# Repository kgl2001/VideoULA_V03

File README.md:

# VideoULA V03 — BBC Micro Video ULA Replacement
## 44-pin Atmel ATF1504AS CPLD Version

This repository contains the hardware design and firmware for the VideoULA V03, a drop-in replacement for the VC2069 Video ULA (IC6) in the Acorn BBC Micro Model B and Master 128.

---

## Project Overview

The original BBC Micro Video ULA (IC6) is a custom ASIC that is no longer manufactured. Failed or missing ULAs result in a non-functional machine. This project provides a modern replacement using a CPLD and a small external SRAM for palette storage.

There are three hardware versions of this replacement, each in a separate repository:

| Version | CPLD | Macrocells | Tool | Repository |
|---|---|---|---|---|
| V01 | Xilinx XC9572XL-10-VQ44 | 72 | ISE 14.7 | [VideoULA_V01](https://github.com/kgl2001/VideoULA_V01) |
| V02 | Xilinx XC9572XL-10-VQ64 | 72 | ISE 14.7 | [VideoULA_V02](https://github.com/kgl2001/VideoULA_V02) |
| **V03** | Atmel ATF1504AS-10AU44 | 64 | Quartus 13.0 SP1 | This repo |

All three versions share the same 28-pin DIP footprint as the original ULA and are pin-compatible with the BBC Micro motherboard.

---

## V03 Hardware

- **CPLD**: Atmel ATF1504AS-10AU44 (64 macrocells, 5V) — still in production
- **SRAM**: ISSI IS62C256AL-45TLI (32K×8, 5V, TSOP-28, 45ns) — only locations 0-15 and bits 0-3 used
- **Oscillator**: 48MHz SMD oscillator (3225 package, 5V) — optional in 16MHz mode
- **Clock buffer**: 74LVC1G17 (SOT-23) — Schmitt trigger buffer on 16MHz CLK_IN
- **No LDO required** — everything runs at 5V

### Key differences from V01/V02

- **5V CPLD** — ATF1504AS operates at 5V throughout, no LDO required
- **Higher output voltage** — 5V logic outputs directly compatible with Master 128 custom ICs requiring higher logic 1 voltage; no output clock buffering needed
- **Still in production** — ATF1504AS is actively manufactured by Microchip, unlike the obsolete XC9572XL
- **64 macrocells** — slightly fewer than the XC9572XL's 72, but sufficient for the design (53/64 used in both the 48MHz and 16MHz builds)
- **Quartus 13.0 SP1** — uses Altera/Intel Quartus instead of Xilinx ISE
- **Separate CLK_16M and CLK_48M GCK pins** — no solder bridge needed to switch modes

### Hardware Revisions

| Revision | Status | Changes |
|---|---|---|
| Rev01 | Built and tested | Initial release |

---

## Firmware

The firmware is written in Verilog and built using Altera Quartus 13.0 SP1. The same Verilog source file (`CPLD Files/src/VideoULA.v`) is shared between V02 and V03.

The Quartus project targets the `EPM7064STC44-10` device — the Altera MAX7000S equivalent of the ATF1504AS, which Quartus supports natively. The `.pof` output is converted to a `.jed` file using the `pof2jed` utility for programming the ATF1504AS.

### Operating Modes

Two firmware builds are required — one per operating mode. Both CLK_16M and CLK_48M are wired to dedicated GCK pins, so no hardware changes are needed to switch modes — simply reprogram the CPLD with the appropriate `.jed` file.

#### 48MHz Mode (recommended)
- Uses the onboard 48MHz oscillator as the master clock
- Generates all BBC clock outputs (8/4/2/1MHz, CRTC, 6MHz) internally
- Provides clean, phase-locked 6MHz output for the SAA5050 teletext chip (tD ≈ 20ns ✓)
- Works reliably on all machines from cold power-up
- Build: uncomment `` `define CLK_48MHZ `` in `VideoULA.v`

#### 16MHz Mode
- Uses the BBC motherboard's 16MHz clock as the master clock (via Schmitt trigger buffer)
- The 48MHz oscillator is optional in 16MHz mode:
  - **Not fitted**: BBC's existing 6MHz circuit drives the SAA5050 as normal
  - **Fitted**: CPLD generates clean phase-locked 6MHz output (connect via IC37 replacement board)
- Build: uncomment `` `define CLK_16MHZ `` in `VideoULA.v`

### Quartus Build Instructions

1. Open Altera Quartus 13.0 SP1
2. Open `VideoULA.qpf`
3. Select the operating mode by uncommenting the appropriate `define` in `src/VideoULA.v`
4. Run `Start Compilation` (Ctrl+L)
5. Convert the output `.pof` file and program the ATF1504AS using the V03 programmer board (see below)

The full toolchain and programming steps (Windows) are in [`CPLD Files/README.md`](CPLD%20Files/README.md).

### Programming the ATF1504AS

Unlike V01 and V02, the V03 board does not have an onboard JTAG connector. This is because the ATF1504AS shares its JTAG pins with I/O pins used by the BBC Micro bus interface — they cannot be used for JTAG programming while the board is installed in the computer.

To program the V03 board, a dedicated programmer board is required. This programmer:

- Accepts the V03 VideoULA board as a plug-in module
- Is powered from the BBC Micro auxiliary power socket (Molex +5V/+12V connector)
- Has a switch to select between normal I/O mode and JTAG programming mode
- Has a standard JTAG header for connection to a compatible JTAG programmer

The KiCAD design files for the programmer board and FreeCAD design files for a suitable enclosure are included in this repository.

**Programming procedure:**
1. Remove the V03 board from the BBC Micro
2. Insert the V03 board into the programmer
3. Connect the programmer to the BBC Micro auxiliary power socket
4. Connect a JTAG programmer to the JTAG header on the programmer board
5. Set the switch to JTAG programming mode
6. Program the CPLD as described in [`CPLD Files/README.md`](CPLD%20Files/README.md)
7. Set the switch back to I/O mode
8. Remove the V03 board from the programmer and reinstall in the BBC Micro

### Quartus Warning Suppression

The following warnings are suppressed in the `.qsf` and are expected/harmless:

| Message | Reason |
|---|---|
| 15705 | Unused clock port pin assignment (expected when only one clock mode is built) |
| 20028 | Parallel compilation not licensed — informational only |
| 199027 | Output file format — `.pof` is generated correctly |
| 332174, 332049 | Timing analysis informational messages |
| 335095 | TimeQuest latch analysis — no latches in design |

---

## SRAM Wiring

The external SRAM stores the 16-entry colour palette (4 bits per entry):

| SRAM Pin | Connection |
|---|---|
| A0-A3 | CPLD SRAM_ADDR[0:3] |
| A4-A14 | GND (tie low) |
| D0-D3 | CPLD SRAM_DATA[0:3] (bidirectional) |
| D4-D7 | Leave unconnected |
| /WE | CPLD SRAM_nWE |
| /OE | GND (always output enabled) |
| /CS | GND (always selected) |

---

## 6MHz Clock for Mode 7 (Teletext)

- **48MHz mode**: CLK_6M pin provides clean phase-locked 6MHz (tD ≈ 20ns ✓). Connect to SAA5050 via IC37 replacement board.
- **16MHz mode, oscillator fitted**: CLK_6M provides clean phase-locked 6MHz, self-correcting every 1µs. Connect via IC37 replacement board.
- **16MHz mode, oscillator not fitted**: CLK_6M output ignored. BBC motherboard's existing 6MHz circuit used as normal.

If the motherboard derives the 6MHz itself (CLK_6M not connected to the SAA5050), the mode 7 cursor may be one pixel too far right on some Model B machines. Feeding the CPLD's CLK_6M directly to the teletext IC avoids this.

---

## PCB Design Notes

The PCB has been designed using KiCAD V10 as a 2-layer board. It can easily be changed to a 4-layer board with GND/Power planes on the inner layers if signal integrity is a concern.

### JLCPCB Fabrication

The board design includes a 5×5mm silkscreen box on the underside of the PCB. This is used by JLCPCB to position a QR code serial number. When ordering from JLCPCB:

- Select **Specify position** in the QR code / 2D barcode options during the ordering process
- If this option is not selected, JLCPCB will print the 5×5mm silkscreen box as-is and attempt to place the QR code at a different location of their choosing

If not using JLCPCB, the chosen fabricator will likely print the 5×5mm box as a plain white square on the PCB. To avoid this, remove the silkscreen box from the PCB design and regenerate the Gerber files before submitting.

### Assembly

A combined CPL (Component Placement List) and BOM (Bill of Materials) Excel file is included in the Gerbers folder. This can be used directly with the JLCPCB PCBA (PCB Assembly) service.

Note that the JLCPCB Economy PCBA process only assembles components on one side of the PCB. Select the **top side** for assembly — this leaves only the SRAM and its associated decoupling capacitor to be hand soldered to the underside of the board.

---

## Known Limitations

- **Mode 7 cursor on some Model B machines**: if the motherboard derives the 6MHz itself, the mode 7 cursor may be one pixel too far right. Feed the CPLD's CLK_6M directly to the teletext IC to avoid this (see the 6MHz Clock section).

---

## Compatibility

Designed for BBC Micro Model B and Master 128. The 5V CPLD outputs are directly compatible with the higher logic 1 voltage required by some Master 128 custom ICs.

---

## Credits

- **Ken Lowe** — PCB design, Verilog development and testing
- **hoglet (Stardot forums)** — Clock architecture analysis, DRAM timing analysis, community testing
- **Stardot community** — Testing, feedback and suggestions

---

## Licence

Hardware: [Creative Commons BY-SA 4.0](https://creativecommons.org/licenses/by-sa/4.0/)

Firmware: [MIT Licence](https://opensource.org/licenses/MIT)

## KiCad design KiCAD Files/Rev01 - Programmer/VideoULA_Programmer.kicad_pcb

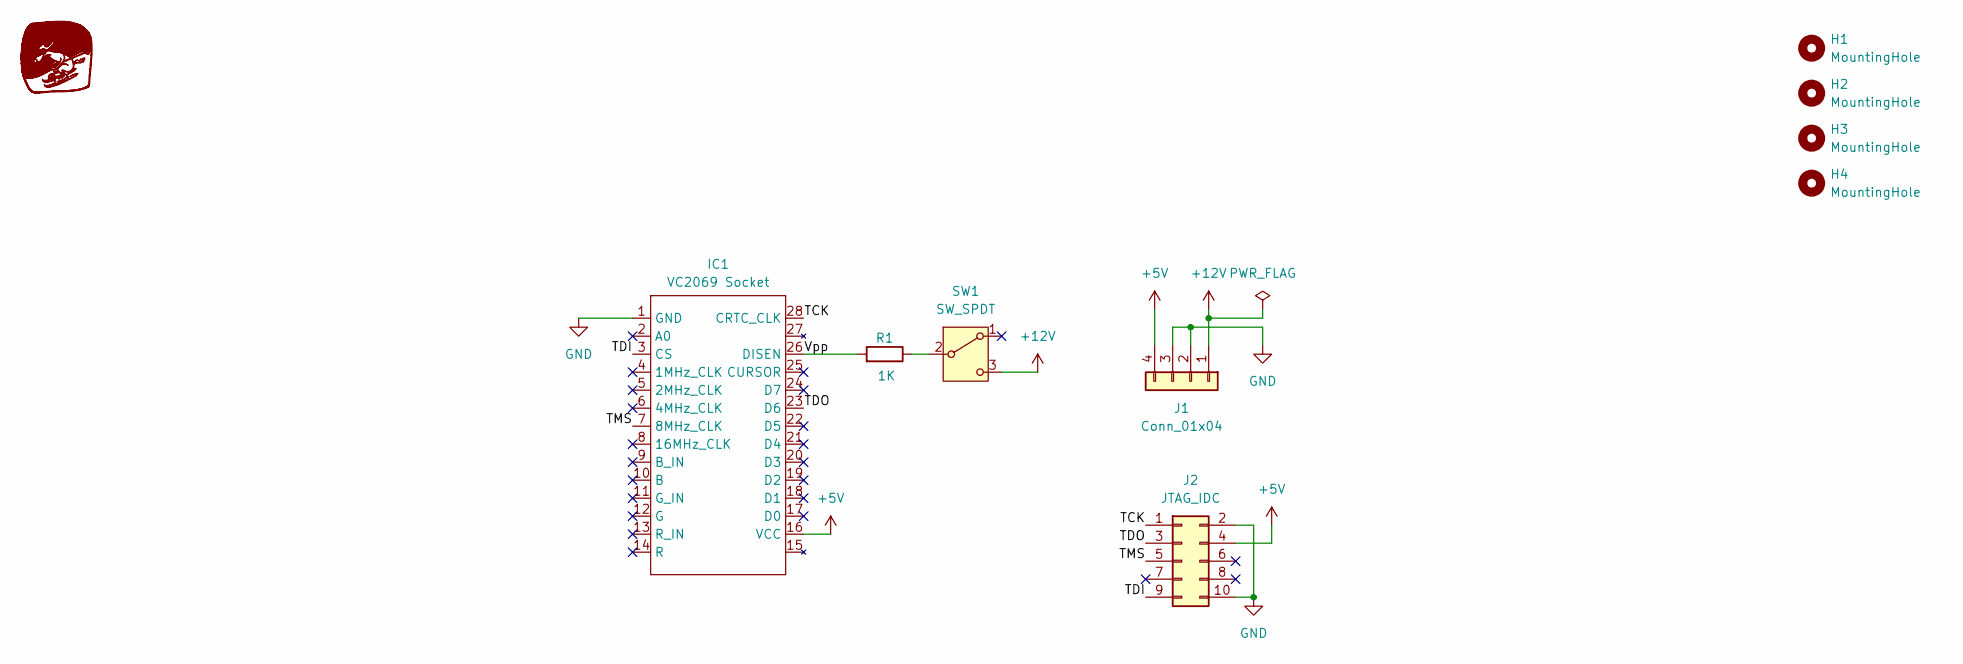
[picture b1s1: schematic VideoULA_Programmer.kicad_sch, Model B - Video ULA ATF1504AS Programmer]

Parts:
G1: Skidog; skidog_inv
H1, H2, H3, H4: MountingHole; MountingHole_2.7mm_M2.5_ISO14580
IC1: VC2069 Socket; DIP-28_W15.24mm_Socket
J1: Conn_01x04; conn_hdd_15-24-4441
J2: JTAG_IDC; PinHeader_2x05_P2.54mm_Vertical
R1: 1K; R_Axial_DIN0207_L6.3mm_D2.5mm_P10.16mm_Horizontal
SW1: SW_SPDT; SW_SS12D00

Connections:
+5V: IC1.16 (VCC), J1.4, J2.4
+12V: J1.1, SW1.3 (C)
/TCK: IC1.28 (CRTC_CLK), J2.1
/TDI: IC1.3 (CS), J2.9
/TDO: IC1.23 (D6), J2.3
/TMS: IC1.7 (8MHz_CLK), J2.5
/Vpp: IC1.26 (DISEN), R1.2
GND: IC1.1 (GND), J1.2, J1.3, J2.2, J2.10
unnamed: R1.1, SW1.2 (B)

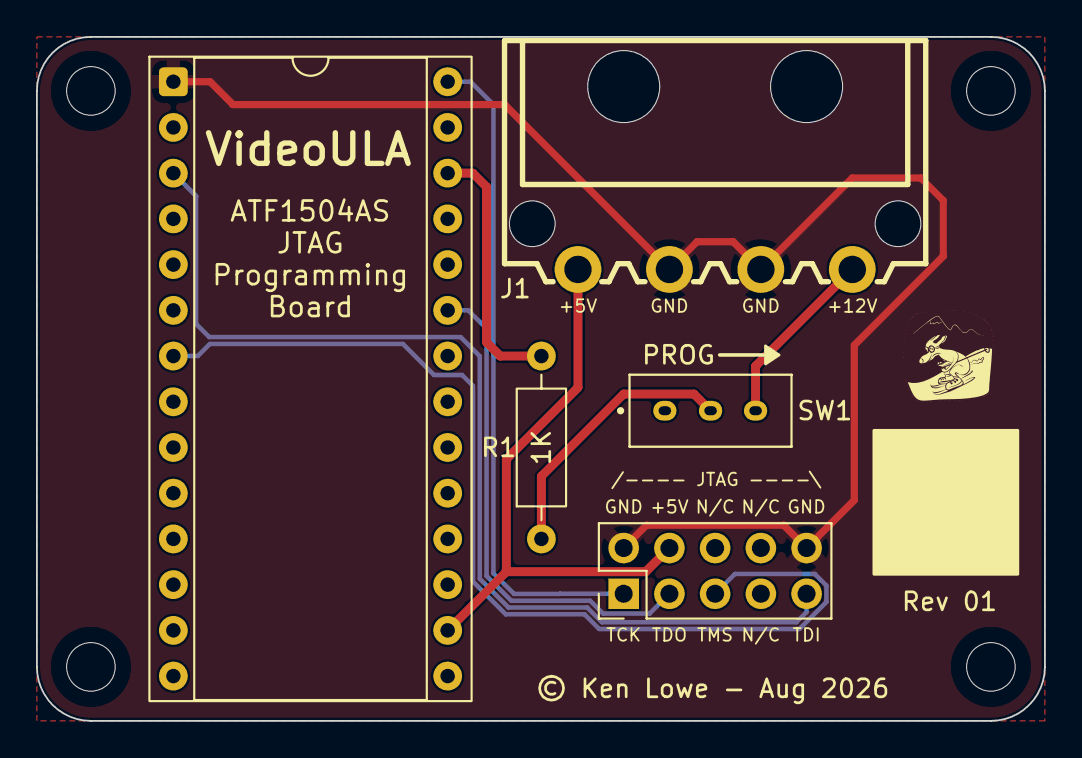
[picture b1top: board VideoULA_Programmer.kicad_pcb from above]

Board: 2 copper layers, 56.0 x 38.0 mm, 10 parts (0 on the bottom side), 9 nets.

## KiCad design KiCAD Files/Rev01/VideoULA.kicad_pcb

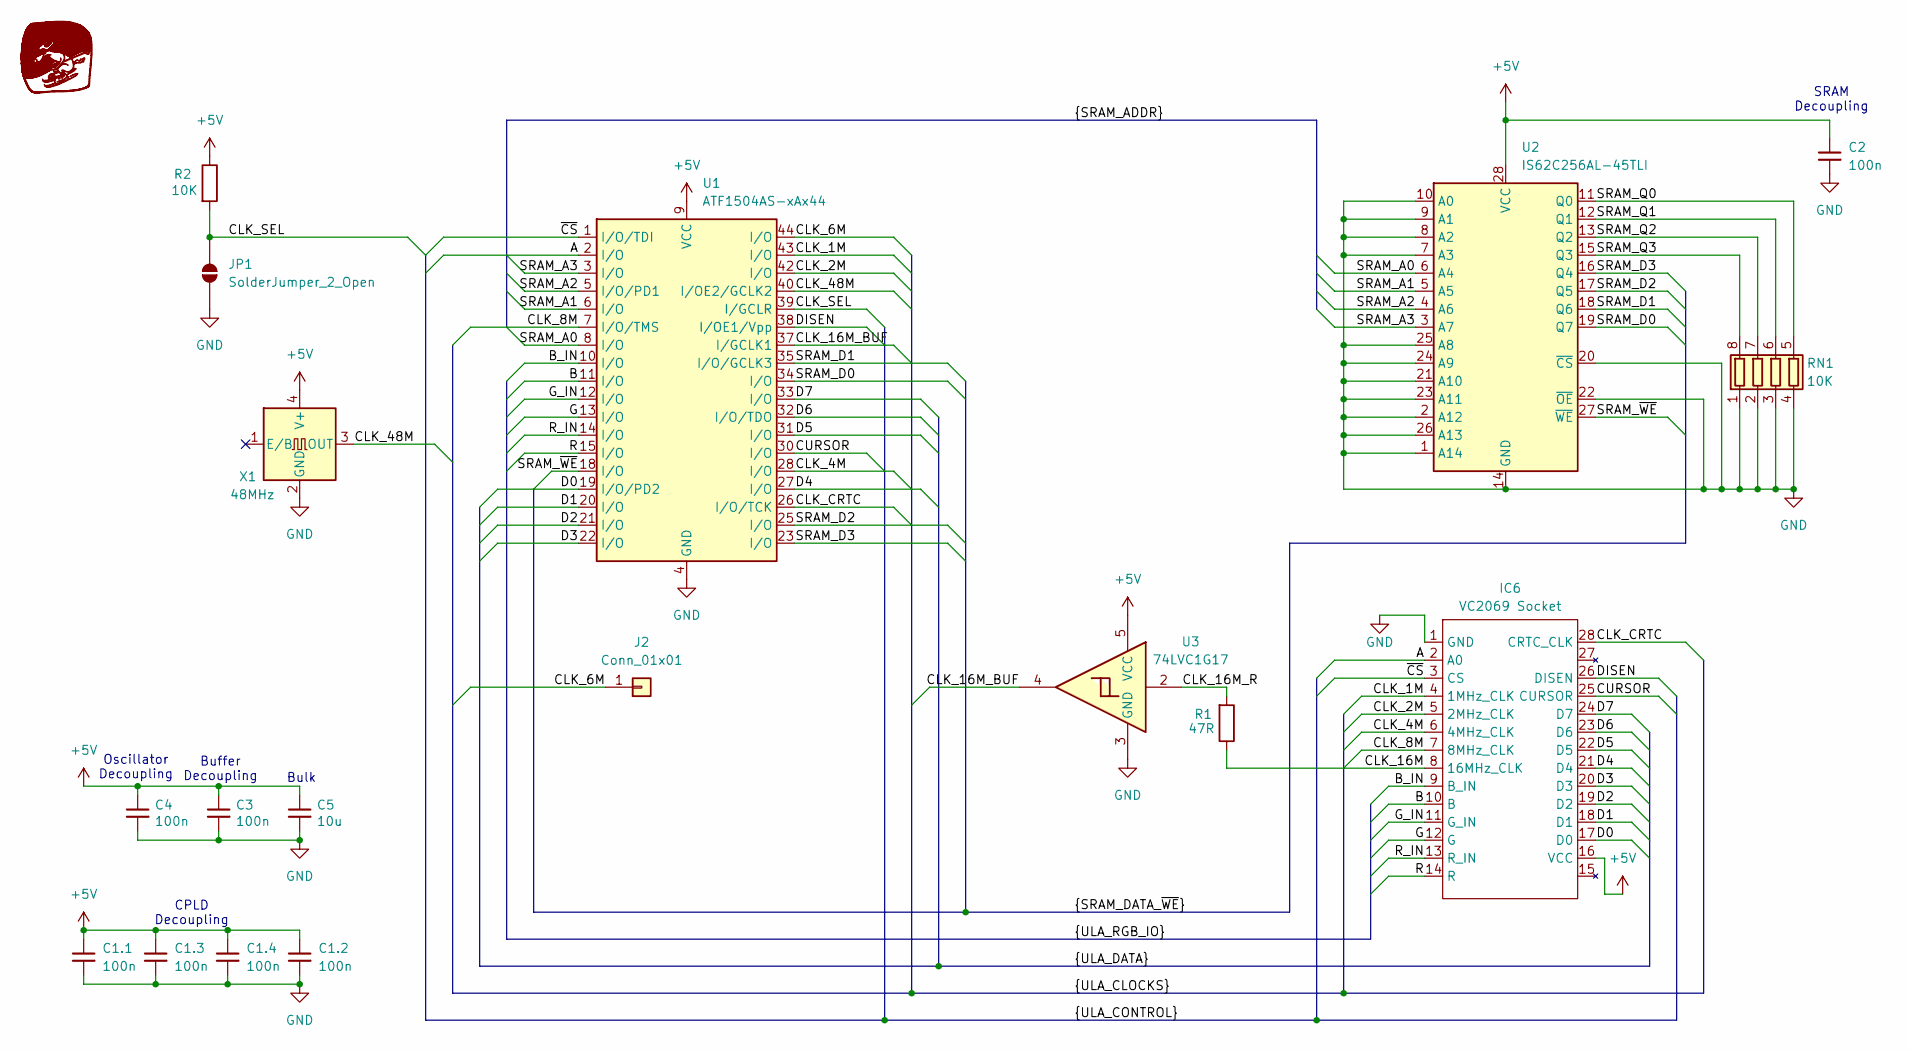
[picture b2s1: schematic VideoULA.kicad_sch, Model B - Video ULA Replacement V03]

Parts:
C1.1, C1.2, C1.3, C1.4, C2, C3, C4: 100n; C_0603_1608Metric; JLC Part Number C14663
C5: 10u; C_0603_1608Metric; JLC Part Number C19702
G1: Skidog; skidog_inv
IC6: VC2069 Socket; DIP-28_W15.24mm
J2: Conn_01x01; PinHeader_1x01_P2.54mm_Horizontal
JP1: SolderJumper_2_Open; SolderJumper-2_P1.3mm_Open_RoundedPad1.0x1.5mm
R1: 47R; R_0603_1608Metric; JLC Part Number C23182
R2: 10K; R_0603_1608Metric; JLC Part Number C25804
RN1: 10K; R_Array_Convex_4x0603; JLC Part Number C29718
U1: ATF1504AS-xAx44; TQFP-44_10x10mm_P0.8mm; JLC Part Number C219301
U2: IS62C256AL-45TLI; TSOP-I-28_11.8x8mm_P0.55mm_SRAM; JLC Part Number C47143
U3: 74LVC1G17; SOT-23-5; JLC Part Number C151394
X1: 48MHz; Oscillator_SMD_Yajingxin_TFOM48M4RHKCNT2T-4Pin_3.2x2.5mm; JLC Part Number C454614

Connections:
+5V: C1.1.1, C1.2.1, C1.3.1, C1.4.1, C2.1, C3.1, C4.1, C5.1, IC6.16 (VCC), R2.1, U1.9 (VCC), U1.17 (VCC), U1.29 (VCC), U1.41 (VCC), U2.28 (VCC), U3.5 (VCC), X1.4 (V+)
/A: IC6.2 (A0), U1.2 (I/O)
/B: IC6.10 (B), U1.11 (I/O)
/B_IN: IC6.9 (B_IN), U1.10 (I/O)
/CLK_1M: IC6.4 (1MHz_CLK), U1.43 (I/O)
/CLK_2M: IC6.5 (2MHz_CLK), U1.42 (I/O)
/CLK_4M: IC6.6 (4MHz_CLK), U1.28 (I/O)
/CLK_6M: J2.1 (Pin_1_1), U1.44 (I/O)
/CLK_8M: IC6.7 (8MHz_CLK), U1.7 (I/O/TMS)
/CLK_16M: IC6.8 (16MHz_CLK), R1.1
/CLK_16M_BUF: U1.37 (I/GCLK1), U3.4
/CLK_16M_R: R1.2, U3.2
/CLK_48M: U1.40 (I/OE2/GCLK2), X1.3 (OUT)
/CLK_CRTC: IC6.28 (CRTC_CLK), U1.26 (I/O/TCK)
/CLK_SEL: JP1.2 (B), R2.2, U1.39 (I/GCLR)
/CURSOR: IC6.25 (CURSOR), U1.30 (I/O)
/D0: IC6.17 (D0), U1.19 (I/O/PD2)
/D1: IC6.18 (D1), U1.20 (I/O)
/D2: IC6.19 (D2), U1.21 (I/O)
/D3: IC6.20 (D3), U1.22 (I/O)
/D4: IC6.21 (D4), U1.27 (I/O)
/D5: IC6.22 (D5), U1.31 (I/O)
/D6: IC6.23 (D6), U1.32 (I/O/TDO)
/D7: IC6.24 (D7), U1.33 (I/O)
/DISEN: IC6.26 (DISEN), U1.38 (I/OE1/Vpp)
/G: IC6.12 (G), U1.13 (I/O)
/G_IN: IC6.11 (G_IN), U1.12 (I/O)
/R: IC6.14 (R), U1.15 (I/O)
/R_IN: IC6.13 (R_IN), U1.14 (I/O)
/SRAM_A0: U1.8 (I/O), U2.6 (A4)
/SRAM_A1: U1.6 (I/O), U2.5 (A5)
/SRAM_A2: U1.5 (I/O/PD1), U2.4 (A6)
/SRAM_A3: U1.3 (I/O), U2.3 (A7)
/SRAM_D0: U1.34 (I/O), U2.19 (Q7)
/SRAM_D1: U1.35 (I/O/GCLK3), U2.18 (Q6)
/SRAM_D2: U1.25 (I/O), U2.17 (Q5)
/SRAM_D3: U1.23 (I/O), U2.16 (Q4)
/SRAM_Q0: RN1.5 (R4.2), U2.11 (Q0)
/SRAM_Q1: RN1.6 (R3.2), U2.12 (Q1)
/SRAM_Q2: RN1.7 (R2.2), U2.13 (Q2)
/SRAM_Q3: RN1.8 (R1.2), U2.15 (Q3)
/SRAM_~WE: U1.18 (I/O), U2.27 (~WE)
/~CS: IC6.3 (CS), U1.1 (I/O/TDI)
GND: C1.1.2, C1.2.2, C1.3.2, C1.4.2, C2.2, C3.2, C4.2, C5.2, IC6.1 (GND), JP1.1 (A), RN1.1 (R1.1), RN1.2 (R2.1), RN1.3 (R3.1), RN1.4 (R4.1), U1.4 (GND), U1.16 (GND), U1.24 (GND), U1.36 (GND), U2.1 (A14), U2.2 (A12), U2.7 (A3), U2.8 (A2), U2.9 (A1), U2.10 (A0), U2.14 (GND), U2.20 (~CS), U2.21 (A10), U2.22 (~OE), U2.23 (A11), U2.24 (A9), U2.25 (A8), U2.26 (A13), U3.3 (GND), X1.2 (GND)

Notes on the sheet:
SRAM Decoupling
Oscillator Decoupling
CPLD Decoupling
Bulk
Buffer Decoupling

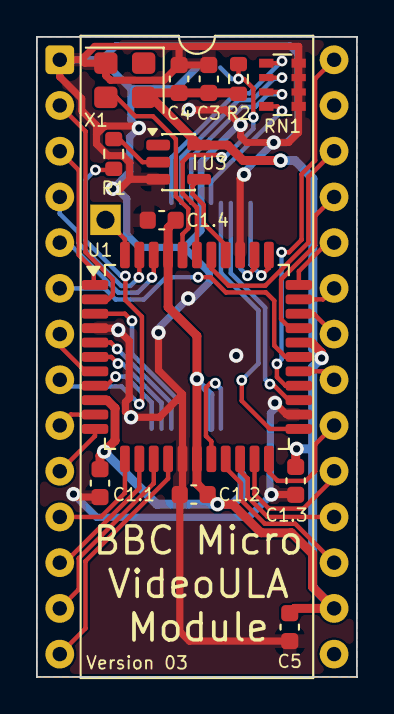
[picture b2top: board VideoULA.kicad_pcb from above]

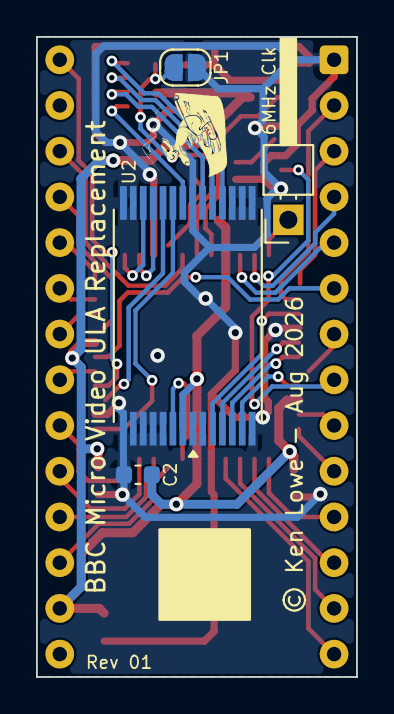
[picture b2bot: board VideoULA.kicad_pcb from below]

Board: 2 copper layers, 17.8 x 35.6 mm, 19 parts (5 on the bottom side), 44 nets.

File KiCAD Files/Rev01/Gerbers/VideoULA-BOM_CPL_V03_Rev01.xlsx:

Designator | Val | Package | Mid X | Mid Y | Rotation | Layer | JLC Part Number
C2 | 100n | C_0603_1608Metric | 88.882531999999998 | -62.929547999999997 | 0 | bottom | C14663
U2 | IS62C256AL-45TLI | TSOP-I-28_11.8x8mm_P0.55mm_SRAM | 86.111000000000004 | -54.097000000000001 | 90 | bottom | C47143
C1.1 | 100n | C_0603_1608Metric | 80.218199999999996 | -63.3934 | -90 | top | C14663
C1.2 | 100n | C_0603_1608Metric | 85.425200000000004 | -64.028400000000005 | 180 | top | C14663
C1.3 | 100n | C_0603_1608Metric | 91.089731999999998 | -63.266348000000001 | -90 | top | C14663
C1.4 | 100n | C_0603_1608Metric | 83.647199999999998 | -48.788400000000003 | 180 | top | C14663
C3 | 100n | C_0603_1608Metric | 86.2624 | -40.939799999999998 | 90 | top | C14663
C4 | 100n | C_0603_1608Metric | 84.612399999999994 | -40.939799999999998 | 90 | top | C14663
C5 | 10u | C_0603_1608Metric | 90.759200000000007 | -71.394400000000005 | -90 | top | C19702
R1 | 47R | R_0603_1608Metric | 80.980199999999996 | -45.105400000000003 | 90 | top | C23182
R2 | 10K | R_0603_1608Metric | 87.912400000000005 | -40.939799999999998 | 90 | top | C25804
RN1 | 10K | R_Array_Convex_4x0603 | 90.355732000000003 | -41.263348000000001 | 90 | top | C29718
U1 | ATF1504AS-xAx44 | TQFP-44_10x10mm_P0.8mm | 85.602999999999994 | -56.383000000000003 | -90 | top | C219301
U3 | 74LVC1G17 | SOT-23-5 | 84.587000000000003 | -45.562600000000003 | -90 | top | C151394
X1 | 48MHz | Oscillator_SMD_Yajingxin_TFOM48M4RHKCNT2T-4Pin_3.2x2.5mm | 81.592731999999998 | -41.009348000000003 | 180 | top | C454614

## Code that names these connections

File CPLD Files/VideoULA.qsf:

# -------------------------------------------------------------------------- #
#
# Copyright (C) 1991-2013 Altera Corporation
# Your use of Altera Corporation's design tools, logic functions 
# and other software and tools, and its AMPP partner logic 
# functions, and any output files from any of the foregoing 
# (including device programming or simulation files), and any 
# associated documentation or information are expressly subject 
# to the terms and conditions of the Altera Program License 
# Subscription Agreement, Altera MegaCore Function License 
# Agreement, or other applicable license agreement, including, 
# without limitation, that your use is for the sole purpose of 
# programming logic devices manufactured by Altera and sold by 
# Altera or its authorized distributors.  Please refer to the 
# applicable agreement for further details.
#
# -------------------------------------------------------------------------- #
#
# Quartus II 64-Bit
# Version 13.0.1 Build 232 06/12/2013 Service Pack 1 SJ Web Edition
# Date created = 22:23:39  August 16, 2026
#
# -------------------------------------------------------------------------- #
#
# Notes:
#
# 1) The default values for assignments are stored in the file:
#		VideoULA_assignment_defaults.qdf
#    If this file doesn't exist, see file:
#		assignment_defaults.qdf
#
# 2) Altera recommends that you do not modify this file. This
#    file is updated automatically by the Quartus II software
#    and any changes you make may be lost or overwritten.
#
# -------------------------------------------------------------------------- #


set_global_assignment -name FAMILY MAX7000S
set_global_assignment -name DEVICE "EPM7064STC44-10"
set_global_assignment -name TOP_LEVEL_ENTITY VideoULA
set_global_assignment -name ORIGINAL_QUARTUS_VERSION "13.0 SP1"
set_global_assignment -name PROJECT_CREATION_TIME_DATE "22:23:39  AUGUST 16, 2026"
set_global_assignment -name LAST_QUARTUS_VERSION "13.0 SP1"
set_global_assignment -name PROJECT_OUTPUT_DIRECTORY output_files
set_global_assignment -name ERROR_CHECK_FREQUENCY_DIVISOR "-1"
set_global_assignment -name EDA_DESIGN_ENTRY_SYNTHESIS_TOOL "Design Compiler"
set_global_assignment -name EDA_INPUT_VCC_NAME VDD -section_id eda_design_synthesis
set_global_assignment -name EDA_LMF_FILE altsyn.lmf -section_id eda_design_synthesis
set_global_assignment -name EDA_INPUT_DATA_FORMAT "VERILOG HDL" -section_id eda_design_synthesis
set_global_assignment -name OPTIMIZE_HOLD_TIMING OFF
set_global_assignment -name OPTIMIZE_MULTI_CORNER_TIMING OFF
set_global_assignment -name FITTER_EFFORT "STANDARD FIT"
set_global_assignment -name MAX7000_DEVICE_IO_STANDARD TTL
set_global_assignment -name MAX7000_ENABLE_JTAG_BST_SUPPORT OFF
set_global_assignment -name USE_CONFIGURATION_DEVICE ON
set_global_assignment -name MESSAGE_DISABLE 15705
set_global_assignment -name MESSAGE_DISABLE 20028
set_global_assignment -name MESSAGE_DISABLE 199027
set_global_assignment -name MESSAGE_DISABLE 332174
set_global_assignment -name MESSAGE_DISABLE 332049
set_global_assignment -name MESSAGE_DISABLE 335095
set_location_assignment PIN_11 -to B
set_location_assignment PIN_1 -to nCS
set_location_assignment PIN_2 -to A
set_location_assignment PIN_3 -to SRAM_ADDR[3]
set_location_assignment PIN_5 -to SRAM_ADDR[2]
set_location_assignment PIN_6 -to SRAM_ADDR[1]
set_location_assignment PIN_7 -to CLK_8M
set_location_assignment PIN_8 -to SRAM_ADDR[0]
set_location_assignment PIN_10 -to B_IN
set_location_assignment PIN_12 -to G_IN
set_location_assignment PIN_13 -to G
set_location_assignment PIN_14 -to R_IN
set_location_assignment PIN_15 -to R
set_location_assignment PIN_18 -to SRAM_nWE
set_location_assignment PIN_19 -to D[0]
set_location_assignment PIN_20 -to D[1]
set_location_assignment PIN_21 -to D[2]
set_location_assignment PIN_22 -to D[3]
set_location_assignment PIN_23 -to SRAM_DATA[3]
set_location_assignment PIN_25 -to SRAM_DATA[2]
set_location_assignment PIN_26 -to CLK_CRTC
set_location_assignment PIN_27 -to D[4]
set_location_assignment PIN_28 -to CLK_4M
set_location_assignment PIN_30 -to CURSOR
set_location_assignment PIN_31 -to D[5]
set_location_assignment PIN_32 -to D[6]
set_location_assignment PIN_33 -to D[7]
set_location_assignment PIN_34 -to SRAM_DATA[0]
set_location_assignment PIN_35 -to SRAM_DATA[1]
set_location_assignment PIN_38 -to DISEN
set_location_assignment PIN_42 -to CLK_2M
set_location_assignment PIN_43 -to CLK_1M
set_location_assignment PIN_44 -to CLK_6M
set_location_assignment PIN_37 -to CLK_16M
set_location_assignment PIN_40 -to CLK_48M
set_global_assignment -name VERILOG_FILE src/VideoULA.v

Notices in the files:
KiCAD Files/Rev01 - Programmer/VideoULA_Programmer.kicad_pcb:
© Ken Lowe - Aug 2026
